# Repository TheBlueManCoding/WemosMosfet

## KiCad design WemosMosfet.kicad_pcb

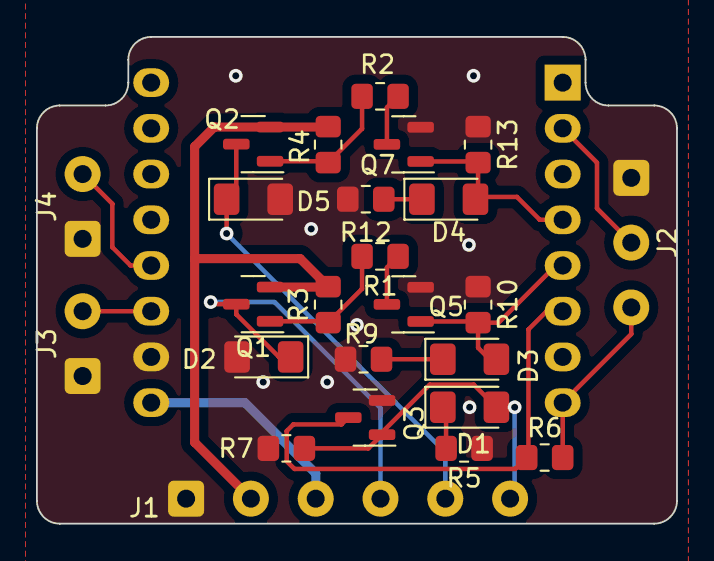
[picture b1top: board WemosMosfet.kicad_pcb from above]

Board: 2 copper layers, 35.6 x 27.0 mm, 26 parts (1 on the bottom side), 20 nets.

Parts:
D1, D3, D4: LED; LED_1206_3216Metric_Pad1.42x1.75mm_HandSolder
D2, D5: LL4148; D_1206_3216Metric_Pad1.42x1.75mm_HandSolder
J1: MIST; SolderWire-0.1sqmm_1x06_P3.6mm_D0.4mm_OD1mm
J2: ADC_1; SolderWire-0.1sqmm_1x03_P3.6mm_D0.4mm_OD1mm
J3: KEY_2; SolderWire-0.1sqmm_1x02_P3.6mm_D0.4mm_OD1mm
J4: KEY_1; SolderWire-0.1sqmm_1x02_P3.6mm_D0.4mm_OD1mm
Q1, Q2: BSS84; SOT-23
Q3, Q5, Q7: BSS138; SOT-23
R1, R2: 18K; R_0805_2012Metric_Pad1.20x1.40mm_HandSolder
R3, R4, R6, R7, R10, R13: 10K; R_0805_2012Metric_Pad1.20x1.40mm_HandSolder
R5, R9, R12: 470R; R_0805_2012Metric_Pad1.20x1.40mm_HandSolder
U1: WeMos_D1_mini; WEMOS_D1_mini_light

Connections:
+3.3V: J2.3, R6.2, U1.8 (3V3)
+5V: J1.3, U1.9 (5V)
+24V: J1.2, Q1.2 (S), Q2.2 (S), R3.2, R4.2
ADC_1: J2.2, U1.2 (A0)
GND: D2.2 (A), D5.2 (A), J1.1, J2.1, J3.1, J4.1, Q3.2 (S), Q5.2 (S), Q7.2 (S), R5.1, R7.1, R9.1, R10.1, R12.1, R13.1, U1.10 (GND)
KEY_1: J4.2, U1.12 (D3)
KEY_2: J3.2, U1.11 (D4)
MIST_AIR: D2.1 (K), J1.4, Q1.3 (D)
MIST_AIR_3V3: D3.2 (A), Q5.1 (G), R10.2, U1.5 (MISO/D6)
MIST_VALVE: D5.1 (K), J1.5, Q2.3 (D)
MIST_VALVE_3V3: D4.2 (A), Q7.1 (G), R13.2, U1.4 (SCK/D5)
unnamed: D1.1 (K), R5.2
unnamed: D3.1 (K), R9.2
unnamed: D4.1 (K), R12.2
unnamed: Q1.1 (G), R1.2, R3.1
unnamed: Q2.1 (G), R2.2, R4.1
unnamed: Q3.3 (D), R6.1, U1.6 (MOSI/D7)
unnamed: Q5.3 (D), R1.1
unnamed: Q7.3 (D), R2.1
REMOTE_EN: D1.2 (A), J1.6, Q3.1 (G), R7.2

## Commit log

2023-10-21 Initial commit: - bug in Schematic, dont use it
2023-11-12 Fixed some design flaws, first version didn't work.
